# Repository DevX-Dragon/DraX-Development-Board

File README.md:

# DraX Development Board
A compact, high-performance development board based on the RP2040 microcontroller, designed for versatility with dual power options and easy breadboard integration.

## Layouts

## Renders

## Technical Specifications

**Microcontroller:**
Raspberry Pi RP2040 dual-core ARM Cortex-M0+.

**Storage:** 
16MB (128Mbit) QSPI Flash memory (W25Q128).

**Power Input:** 
Dual-power path with Schottky diode protection (D1, D2).

**USB-C:**
5V via 14-pin USB-C receptacle.

**Battery:**
JST-style connector for LiPo battery support.

**Regulation:**
On-board LDO regulator (NCP1117) providing stable 3.3V.

**Clock:**
12MHz crystal oscillator with 15pF load capacitors.

**I/O:**
40-pin total breakout via dual 20-pin headers (J2, J3) including GPIO and ADC.

**Debugging:**
Dedicated SWD (Serial Wire Debug) header (J4).

**User Interface:**
Tactile Push-buttons for Reset and BOOTSEL modes.

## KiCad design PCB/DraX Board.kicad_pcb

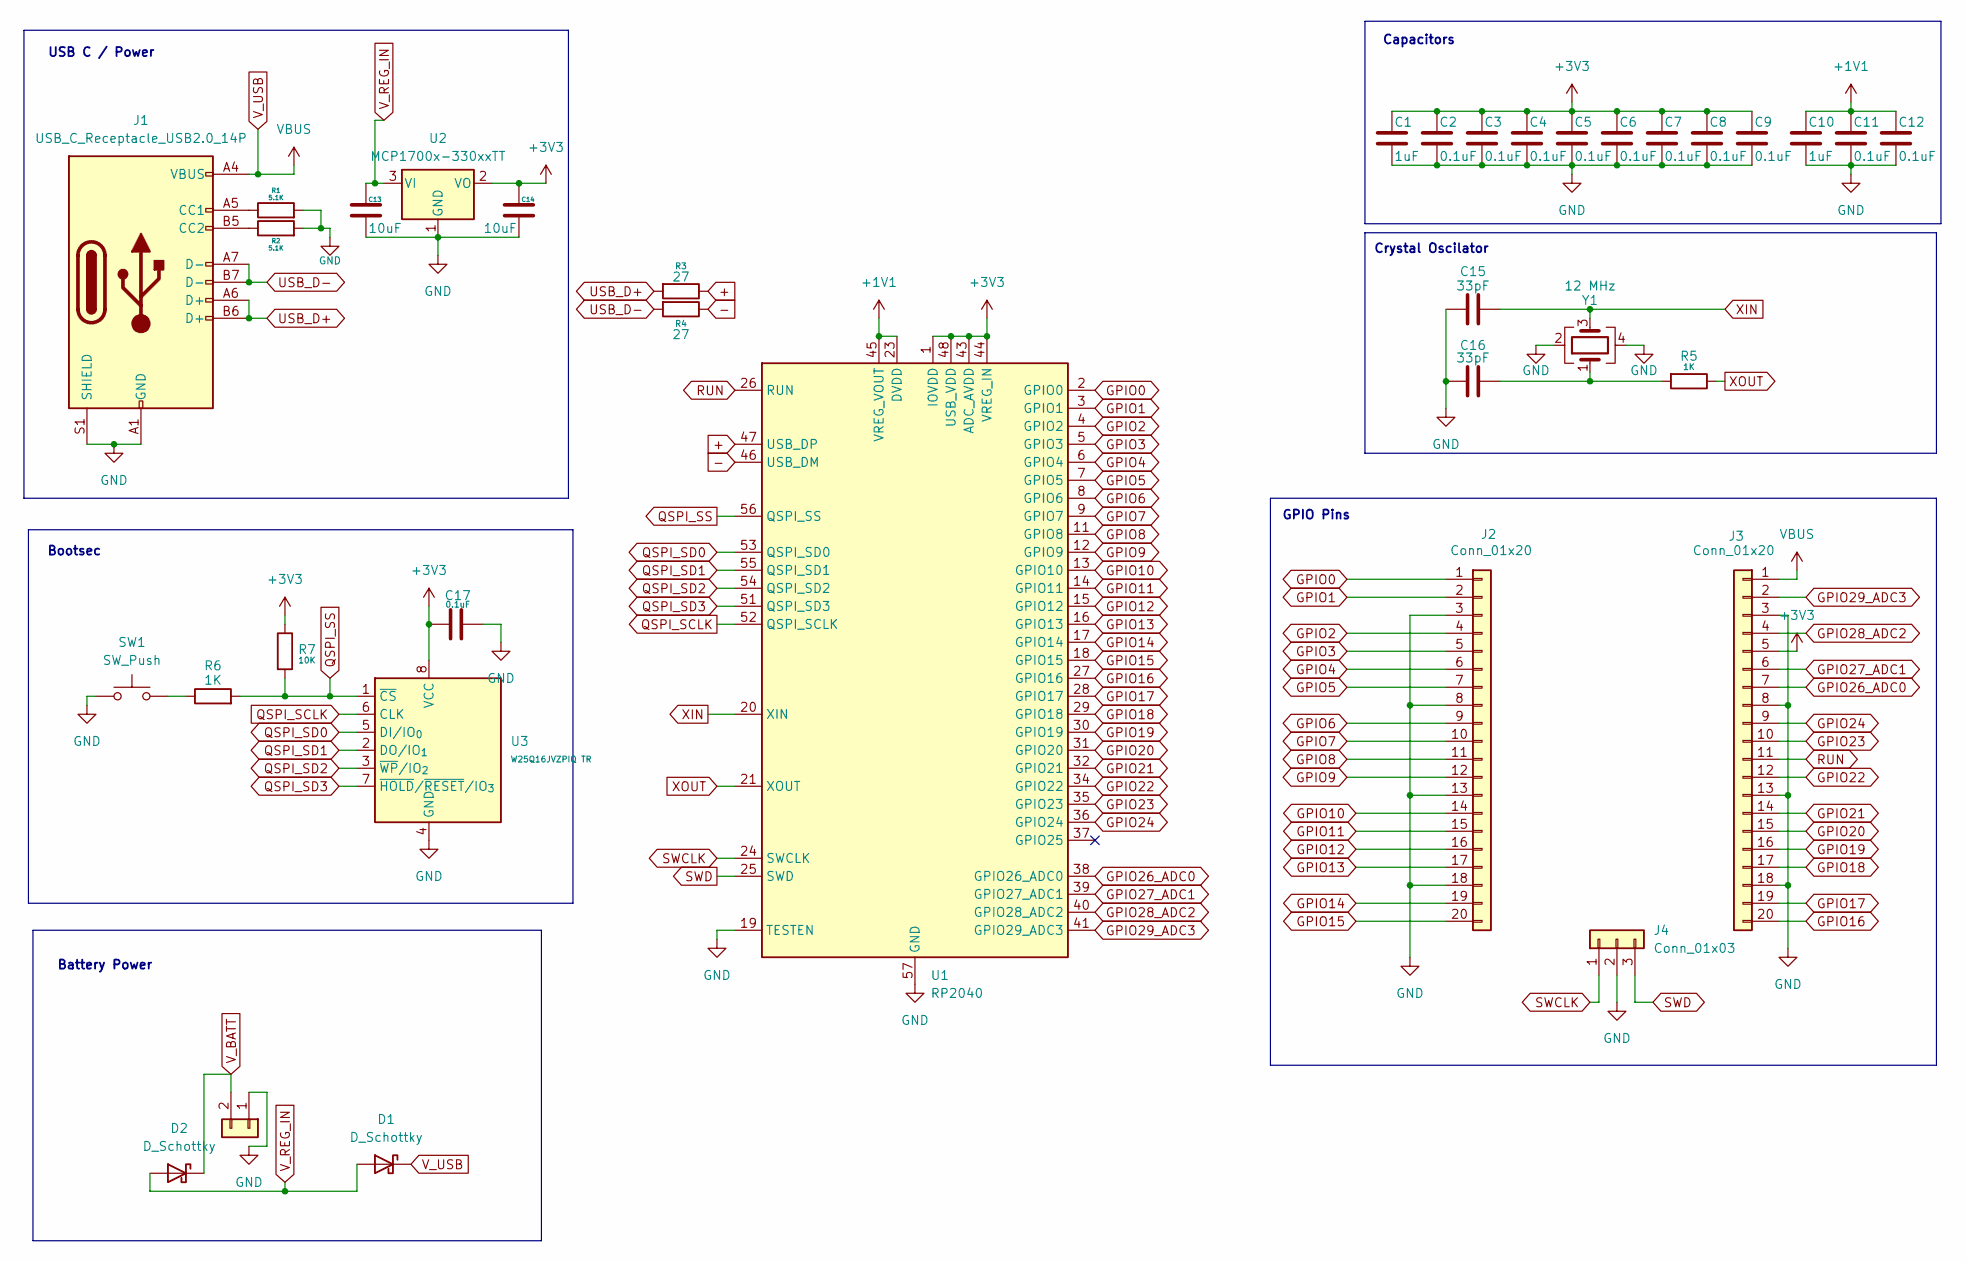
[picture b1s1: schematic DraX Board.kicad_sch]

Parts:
C1, C10: 1uF; C_0402_1005Metric
C2, C3, C4, C5, C6, C7, C8, C9, C11, C12, C17: 0.1uF; C_0402_1005Metric
C13, C14: 10uF; C_0402_1005Metric
C15, C16: 33pF; C_0402_1005Metric
D1, D2: D_Schottky; D_SOD-123
J1: USB_C_Receptacle_USB2.0_14P; USB_C_Receptacle_HRO_TYPE-C-31-M-12
J2, J3: Conn_01x20; PinHeader_1x20_P2.54mm_Vertical
J4: Conn_01x03; PinHeader_1x03_P2.54mm_Vertical
J5: Conn_01x02; PinHeader_1x02_P2.00mm_Horizontal
R1, R2: 5.1K; R_0402_1005Metric
R3, R4: 27; R_0402_1005Metric
R5, R6: 1K; R_0402_1005Metric
R7: 10K; R_0402_1005Metric
SW1: SW_Push; SW_Push_SPST_NO_Alps_SKRK
U1: RP2040; QFN-56-1EP_7x7mm_P0.4mm_EP3.2x3.2mm
U2: MCP1700x-330xxTT; SOT-23
U3: W25Q16JVZPIQ TR; Winbond_USON-8-1EP_3x2mm_P0.5mm_EP0.2x1.6mm
Y1: 12 MHz; Crystal_SMD_3225-4Pin_3.2x2.5mm

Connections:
+: R3.1, U1.47 (USB_DP)
+1V1: C10.1, C11.1, C12.1, U1.23 (DVDD), U1.45 (VREG_VOUT), U1.50 (DVDD)
+3V3: C1.1, C2.1, C3.1, C4.1, C5.1, C6.1, C7.1, C8.1, C9.1, C14.1, C17.1, J3.5, R7.1, U1.1 (IOVDD), U1.10 (IOVDD), U1.22 (IOVDD), U1.33 (IOVDD), U1.42 (IOVDD), U1.43 (ADC_AVDD), U1.44 (VREG_IN), U1.48 (USB_VDD), U1.49 (IOVDD), U2.2 (VO), U3.8 (VCC)
-: R4.1, U1.46 (USB_DM)
GND: C1.2, C2.2, C3.2, C4.2, C5.2, C6.2, C7.2, C8.2, C9.2, C10.2, C11.2, C12.2, C13.2, C14.2, C15.1, C16.1, C17.2, J1.A1 (GND), J1.A12 (GND), J1.B1 (GND), J1.B12 (GND), J1.S1 (SHIELD), J2.3, J2.8, J2.13, J2.18, J3.3, J3.8, J3.13, J3.18, J4.2, J5.1, R1.2, R2.2, SW1.1, U1.19 (TESTEN), U1.57 (GND), U2.1 (GND), U3.4 (GND), Y1.2, Y1.4
GPIO0: J2.1, U1.2 (GPIO0)
GPIO1: J2.2, U1.3 (GPIO1)
GPIO2: J2.4, U1.4 (GPIO2)
GPIO3: J2.5, U1.5 (GPIO3)
GPIO4: J2.6, U1.6 (GPIO4)
GPIO5: J2.7, U1.7 (GPIO5)
GPIO6: J2.9, U1.8 (GPIO6)
GPIO7: J2.10, U1.9 (GPIO7)
GPIO8: J2.11, U1.11 (GPIO8)
GPIO9: J2.12, U1.12 (GPIO9)
GPIO10: J2.14, U1.13 (GPIO10)
GPIO11: J2.15, U1.14 (GPIO11)
GPIO12: J2.16, U1.15 (GPIO12)
GPIO13: J2.17, U1.16 (GPIO13)
GPIO14: J2.19, U1.17 (GPIO14)
GPIO15: J2.20, U1.18 (GPIO15)
GPIO16: J3.20, U1.27 (GPIO16)
GPIO17: J3.19, U1.28 (GPIO17)
GPIO18: J3.17, U1.29 (GPIO18)
GPIO19: J3.16, U1.30 (GPIO19)
GPIO20: J3.15, U1.31 (GPIO20)
GPIO21: J3.14, U1.32 (GPIO21)
GPIO22: J3.12, U1.34 (GPIO22)
GPIO23: J3.10, U1.35 (GPIO23)
GPIO24: J3.9, U1.36 (GPIO24)
GPIO26_ADC0: J3.7, U1.38 (GPIO26_ADC0)
GPIO27_ADC1: J3.6, U1.39 (GPIO27_ADC1)
GPIO28_ADC2: J3.4, U1.40 (GPIO28_ADC2)
GPIO29_ADC3: J3.2, U1.41 (GPIO29_ADC3)
unnamed: C16.2, R5.2, Y1.1
unnamed: J1.A5 (CC1), R1.1
unnamed: J1.B5 (CC2), R2.1
unnamed: R6.1, SW1.2
QSPI_SCLK: U1.52 (QSPI_SCLK), U3.6 (CLK)
QSPI_SD0: U1.53 (QSPI_SD0), U3.5 (DI/IO_{0})
QSPI_SD1: U1.55 (QSPI_SD1), U3.2 (DO/IO_{1})
QSPI_SD2: U1.54 (QSPI_SD2), U3.3 (~WP/IO_{2})
QSPI_SD3: U1.51 (QSPI_SD3), U3.7 (~HOLD/~RESET/IO_{3})
QSPI_SS: R6.2, R7.2, U1.56 (QSPI_SS), U3.1 (~CS)
RUN: J3.11, U1.26 (RUN)
SWCLK: J4.1, U1.24 (SWCLK)
SWD: J4.3, U1.25 (SWD)
USB_D+: J1.A6 (D+), J1.B6 (D+), R3.2
USB_D-: J1.A7 (D-), J1.B7 (D-), R4.2
V_BATT: D2.1 (K), J5.2
V_REG_IN: C13.1, D1.2 (A), D2.2 (A), U2.3 (VI)
V_USB: D1.1 (K), J1.A4 (VBUS), J1.A9 (VBUS), J1.B4 (VBUS), J1.B9 (VBUS), J3.1
XIN: C15.2, U1.20 (XIN), Y1.3
XOUT: R5.1, U1.21 (XOUT)

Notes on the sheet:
GPIO Pins
USB C / Power
Crystal Oscilator
Capacitors
Bootsec
Battery Power

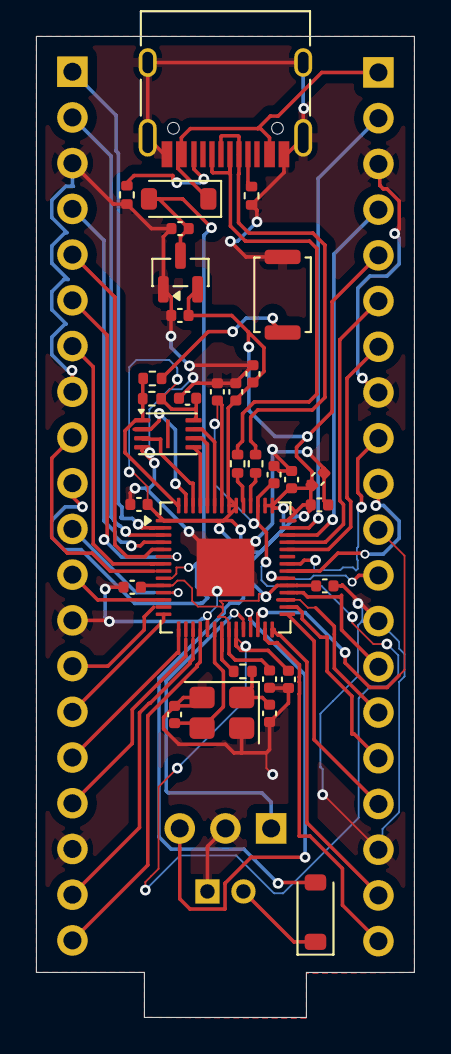
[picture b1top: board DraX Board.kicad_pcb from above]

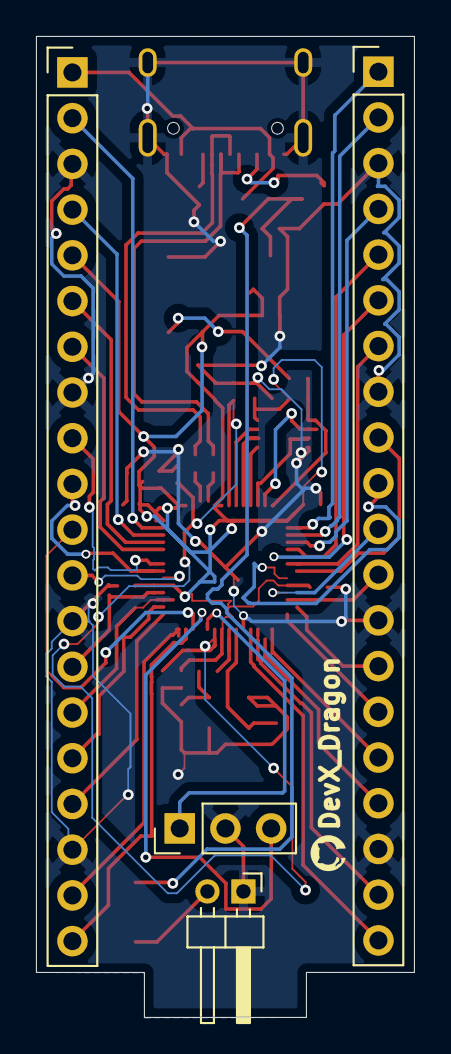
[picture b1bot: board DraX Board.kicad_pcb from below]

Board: 2 copper layers, 21.0 x 54.5 mm, 36 parts (4 on the bottom side), 54 nets.

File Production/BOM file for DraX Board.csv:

Designator,Footprint,Quantity,Comment,Supplier and ref
"C13, C14",C_0402_1005Metric,2,10uF,
"R7, R6",R_0402_1005Metric,2,10K / 1K,
"C8, C4, C11, C7, C12, C5, C17, C9, C3, C2, C6",C_0402_1005Metric,11,0.1uF,
R5,R_0402_1005Metric,1,1K,
"R1, R2",R_0402_1005Metric,2,5.1K,
"R4, R3",R_0402_1005Metric,2,27,
"C16, C15",C_0402_1005Metric,2,33pF,
U3,Winbond_USON-8-1EP_3x2mm_P0.5mm_EP0.2x1.6mm,1,W25Q16JVZPIQ TR,
J1,USB_C_Receptacle_HRO_TYPE-C-31-M-12,1,USB_C_Receptacle_USB2.0_14P,
"C1, C10",C_0402_1005Metric,2,1uF,
U1,QFN-56-1EP_7x7mm_P0.4mm_EP3.2x3.2mm,1,RP2040,
"D1, D2",D_SOD-123,2,D_Schottky,
Y1,Crystal_SMD_3225-4Pin_3.2x2.5mm,1,12 MHz,
U2,SOT-23,1,MCP1700x-330xxTT,
"J3, J2",PinHeader_1x20_P2.54mm_Vertical,2,Conn_01x20,
J4,PinHeader_1x03_P2.54mm_Vertical,1,Conn_01x03,
J5,PinHeader_1x02_P2.00mm_Horizontal,1,Conn_01x02,
SW1,SW_Push_SPST_NO_Alps_SKRK,1,SW_Push,

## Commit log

2026-01-04 Create wow
